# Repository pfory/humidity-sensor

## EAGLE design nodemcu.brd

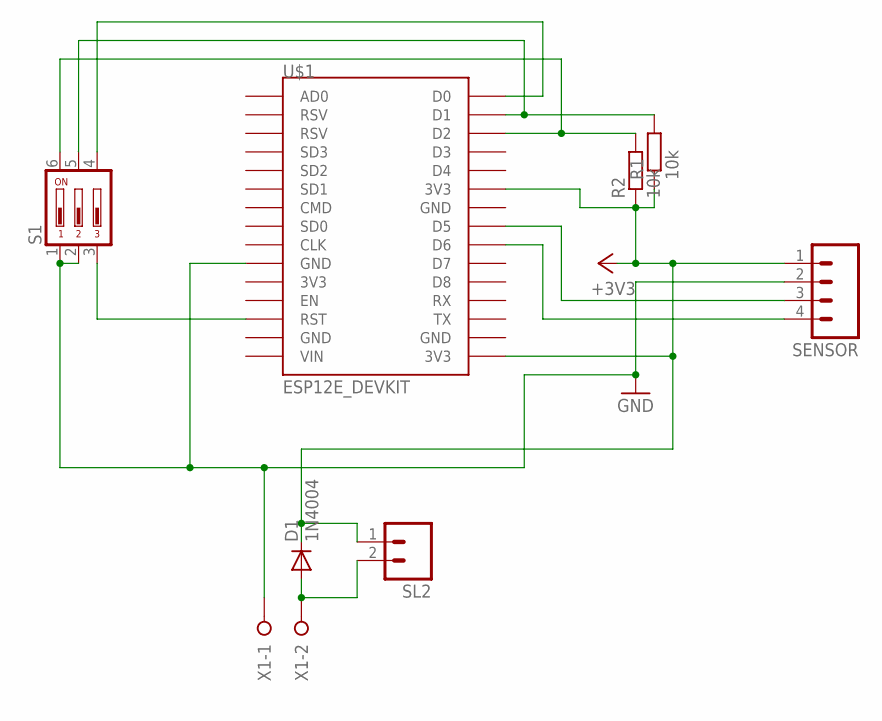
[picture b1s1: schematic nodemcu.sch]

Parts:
D1: 1N4004; DO41-10
R1, R2: 10k; 0207/10
S1: DIP03YL
SENSOR: M04; 04P
SL2: M02; 02P
U$1: ESP12E_DEVKIT
X1: W237-02P; W237-132

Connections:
+3V3: D1.C, R1.1, R2.1, SENSOR.1, SL2.1, U$1.3V3@1 (3V3), U$1.3V3@2 (3V3)
GND: S1.1, S1.2, SENSOR.2, U$1.GND@0 (GND), X1.1
unnamed: S1.4, U$1.D0
unnamed: SENSOR.4, U$1.D6
unnamed: SENSOR.3, U$1.D5
unnamed: S1.3, U$1.RST
unnamed: D1.A, SL2.2, X1.2
unnamed: R1.2, S1.5, U$1.D1
unnamed: R2.2, S1.6, U$1.D2

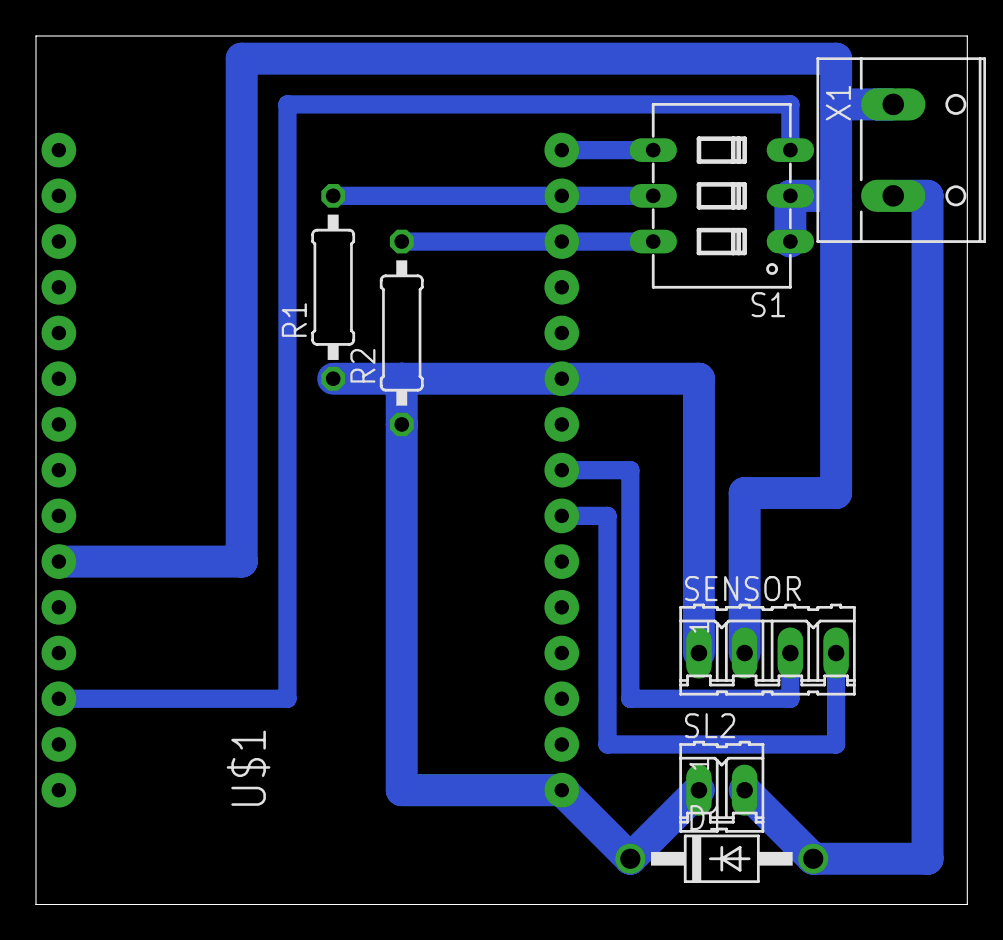
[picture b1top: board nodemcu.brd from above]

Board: 2 copper layers, 51.7 x 48.2 mm, 8 parts (0 on the bottom side), 9 nets.

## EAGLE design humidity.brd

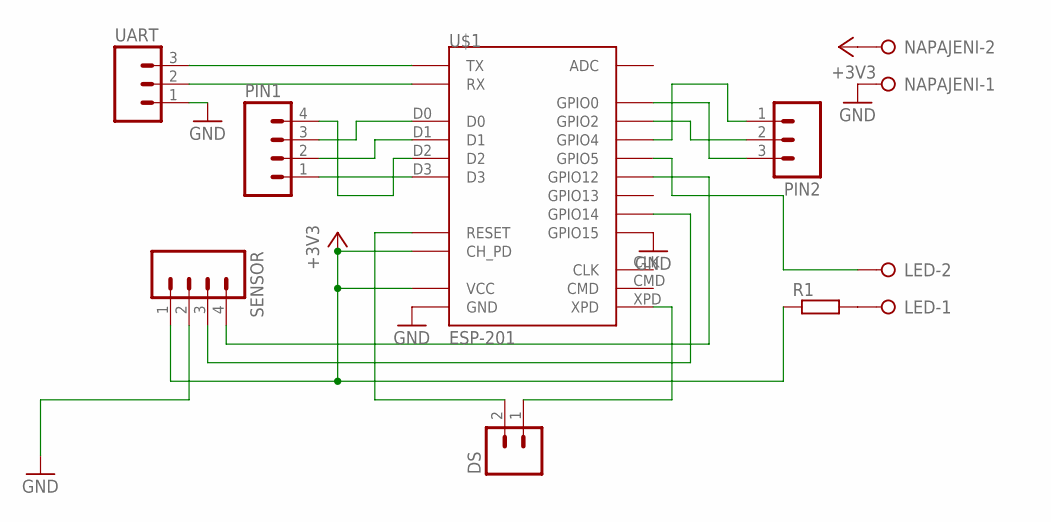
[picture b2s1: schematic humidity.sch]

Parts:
DS: M02; 02P
LED: W237-02P; W237-132
NAPAJENI: W237-02P; W237-132
PIN1: M04; 04P
PIN2: M03; 03P
R1: R-EU_0207/7; 0207/7
SENSOR: M04; 04P
U$1: ESP-201
UART: M03; 03P

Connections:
+3V3: NAPAJENI.2, R1.1, SENSOR.1, U$1.3V3 (VCC), U$1.3V3_2 (VCC), U$1.3V3_3 (VCC), U$1.CH_PD
GND: NAPAJENI.1, SENSOR.2, U$1.GND, U$1.GND_2 (GND), U$1.GND_3 (GND), U$1.GPIO15, UART.1
unnamed: PIN1.1, U$1.D3
unnamed: DS.2, U$1.RST (RESET)
unnamed: SENSOR.3, U$1.GPIO14
unnamed: SENSOR.4, U$1.GPIO12
unnamed: DS.1, U$1.XPD
unnamed: U$1.TX, UART.3
unnamed: U$1.RX, UART.2
unnamed: PIN1.2, U$1.D1
unnamed: PIN1.3, U$1.D0
unnamed: PIN1.4, U$1.D2
unnamed: PIN2.3, U$1.GPIO0
unnamed: PIN2.2, U$1.GPIO2
unnamed: LED.1, R1.2
unnamed: PIN2.1, U$1.GPIO4
unnamed: LED.2, U$1.GPIO5

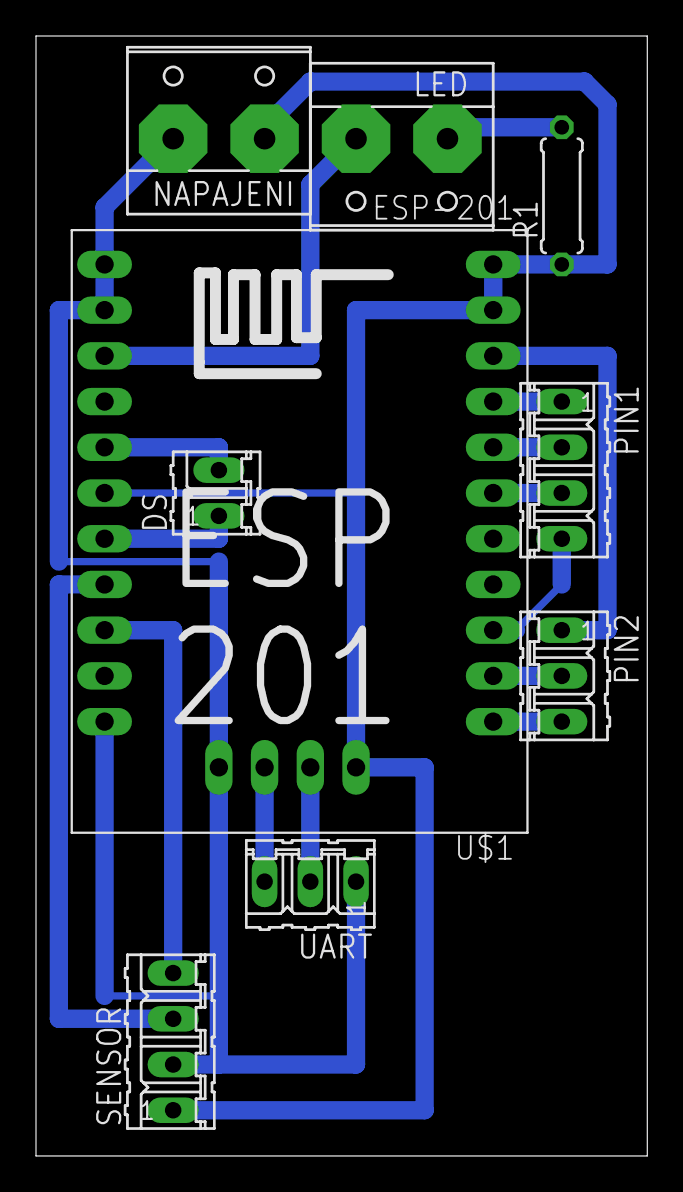
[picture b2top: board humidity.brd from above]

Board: 2 copper layers, 34.0 x 62.2 mm, 9 parts (0 on the bottom side), 17 nets.

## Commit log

2016-04-22 init
2016-04-25 upravena DPS
2016-04-26 +napětí baterie
2016-04-26 +nodemcu
2016-04-27 +nodemcu fw
2016-04-29 +vypocet
2016-05-11 +code for arduino ide
2016-05-12 +pojistka proti vybiti baterie
2016-05-17 v0.3
2016-05-18 v0,31
2016-05-23 funkcni verze pro Holcika - nutno nastavit jeste jeho hodnoty configu
2016-06-03 0,32 - zlepsena ochrana proti vybiti
2016-06-20 +set max Rh to 100
2016-06-28 verze pro Holcika
2016-07-06 v0,33 lua 1.5.1 limit humidity to 100% 6.7.2016
2016-07-06 lua 1.5.1
2016-10-18 v0,33
2016-11-07 +schema a spoj
2016-11-09 uprava desky
2016-11-15 upraveno schema pro dip switch
2016-11-16 upravy spoje
2016-11-22 doplněn návod
2016-11-22 změna tlouštky spojů
2016-11-22 parsing
2016-11-30 prvni zcela funkcni verze
2016-12-01 zmena adc mode
2016-12-01 split ip adresy
2016-12-01 ip adresy z konfigurace
2016-12-07 optimalizace kódu
2016-12-07 prirucka
2016-12-07 +obrazky
2016-12-08 přeskupeno
2016-12-08 +mac
2016-12-09 doplnění dokumentace a obrázku zařízení
2017-03-28 vlhkomer doma
2017-08-08 format kodu
2018-01-11 zmeny konfigurace
2018-01-21 upravy na mqtt
2018-09-06 pridan arduino projekt pro esp8266-201
2018-09-23 zmena ip
2020-07-23 + sensor s deep sleep pro sklenik
2021-01-07 verze pro Arduino IDE a ESP201
2021-06-30 opravena chyba s delkou bootu
